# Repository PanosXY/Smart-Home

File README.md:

# Smart-Home
Smart Home combines a lot of technologies such as Internet, Electronics, Wireless communication, Serial communication, Databases, Raspberry Pi &amp; Linux and several programming languages (Python, PHP, Embedded C)

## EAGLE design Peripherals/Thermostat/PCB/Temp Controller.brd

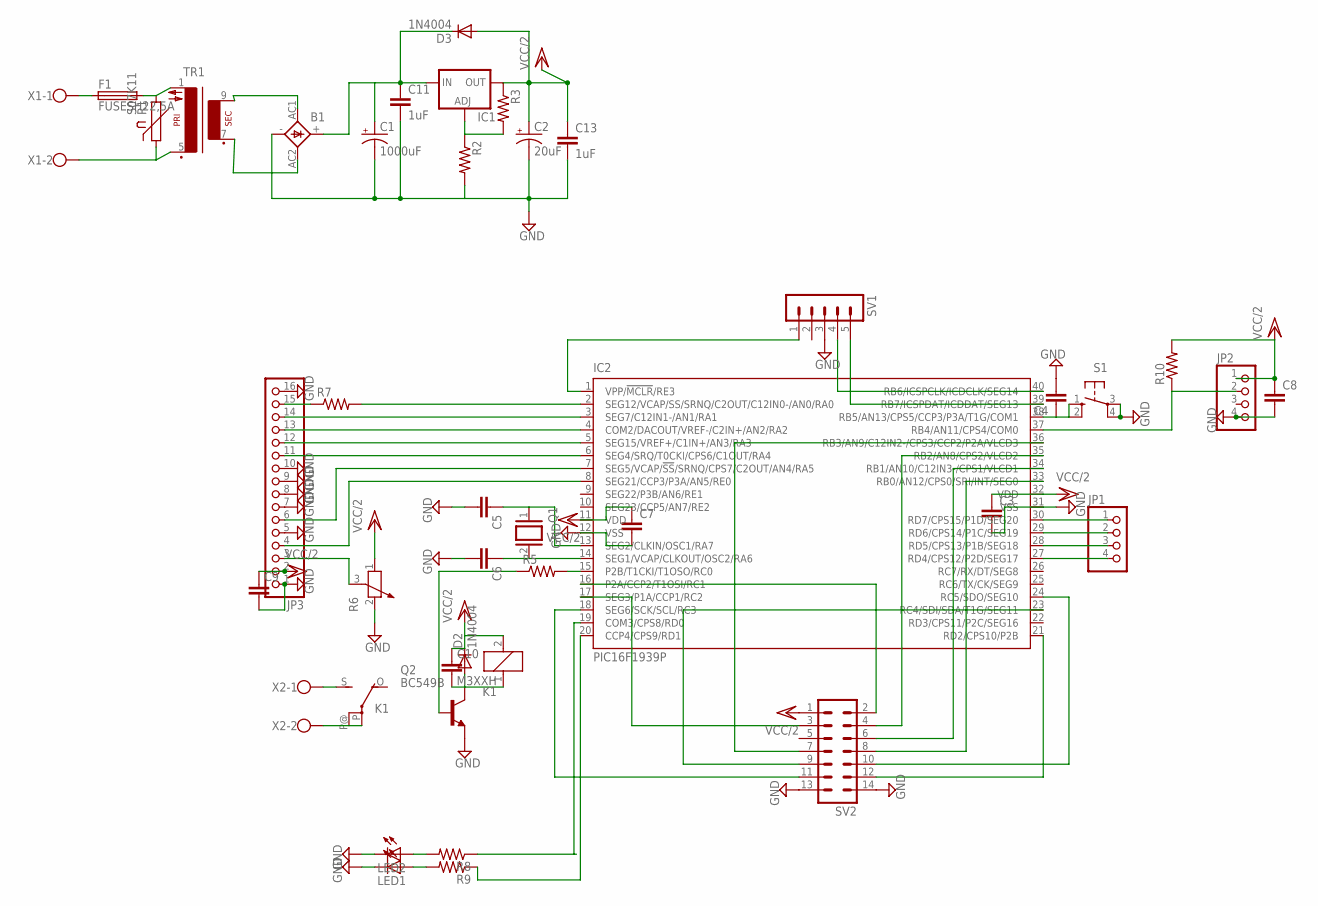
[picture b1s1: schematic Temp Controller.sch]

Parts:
B1: 1KAB
C1: 1000uF; E5-13
C2: 20uF; E5-6
C3, C4, C7, C8, C9, C10: C-EU025-030X050; C025-030X050
C5, C6: C2.5/2; C2.5-2
C11, C13: 1uF; C025-030X050
D2, D3: 1N4004; DO41-10
F1: FUSESH22,5A; SH22,5A
IC1: LM317TS; 317TS
IC2: PIC16F1939P; DIL40
JP1, JP2: PINHD-1X4; 1X04
JP3: PINHD-1X16; 1X16
K1: M3XXH
LED1, LED2: LED3MM
Q1: XTAL/S; QS
Q2: BC549B; TO92-EBC
R1: S07K11
R2, R3, R5, R7, R8, R9, R10: R-US_0207/10; 0207/10
R6: POTENTIOMETER_PT-10; PT-10
S1: 10-XX; B3F-10XX
SV1: MA05-1
SV2: MA07-2
TR1: VV11
X1, X2: W237-02P; W237-132

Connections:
GND: B1.-, C1.-, C2.-, C3.2, C4.2, C5.2, C6.2, C7.2, C8.2, C9.2, C11.2, C13.2, IC2.12 (VSS), IC2.31 (VSS), JP2.4, JP3.1, JP3.5, JP3.7, JP3.8, JP3.9, JP3.10, JP3.16, LED1.K (C), LED2.K (C), Q2.E, R2.2, R6.2, S1.3, S1.4 (P1), SV1.3, SV2.13, SV2.14
unnamed: F1.1, X1.1
unnamed: F1.2, R1.2, TR1.1
unnamed: R1.1, TR1.5 (P2), X1.2
unnamed: IC2.33 (RB0/AN12/CPS0/SRI/INT/SEG0), SV2.8
unnamed: B1.AC1, TR1.9 (S4)
unnamed: B1.AC2, TR1.7 (S3)
unnamed: IC2.30 (RD7/CPS15/P1D/SEG20), JP1.1
unnamed: B1.+, C1.+, C11.1, D3.C, IC1.3 (IN)
unnamed: IC2.34 (RB1/AN10/C12IN3-/CPS1/VLCD1), SV2.6
unnamed: IC2.18 (SEG6/SCK/SCL/RC3), SV2.11
unnamed: IC2.1 (VPP/!MCLR!/RE3), SV1.1
unnamed: IC2.40 (RB6/ICSPCLK/ICDCLK/SEG14), SV1.4
unnamed: IC2.39 (RB7/ICSPDAT/ICDDAT/SEG13), SV1.5
unnamed: C5.1, IC2.13 (SEG2/CLKIN/OSC1/RA7), Q1.1
unnamed: C6.1, IC2.14 (SEG1/VCAP/CLKOUT/OSC2/RA6), Q1.2
unnamed: IC2.2 (SEG12/VCAP/SS/SRNQ/C2OUT/C12IN0-/AN0/RA0), R7.2
unnamed: IC2.29 (RD6/CPS14/P1C/SEG19), JP1.2
unnamed: IC2.23 (RC4/SDI/SDA/T1G/SEG11), SV2.9
unnamed: IC2.24 (RC5/SDO/SEG10), SV2.10
unnamed: IC2.21 (RD2/CPS10/P2B), SV2.12
unnamed: IC2.16 (P2A/CCP2/T1OSI/RC1), SV2.2
unnamed: IC2.17 (SEG3/P1A/CCP1/RC2), SV2.3
unnamed: JP3.15, R7.1
unnamed: IC2.36 (RB3/AN9/C12IN2-/CPS3/CCP2/P2A/VLCD3), SV2.7
unnamed: IC2.35 (RB2/AN8/CPS2/VLCD2), SV2.4
unnamed: IC2.3 (SEG7/C12IN1-/AN1/RA1), JP3.14
unnamed: IC2.4 (COM2/DACOUT/VREF-/C2IN+/AN2/RA2), JP3.13
unnamed: IC2.5 (SEG15/VREF+/C1IN+/AN3/RA3), JP3.12
unnamed: IC2.6 (SEG4/SRQ/T0CKI/CPS6/C1OUT/RA4), JP3.11
unnamed: IC2.7 (SEG5/VCAP/!SS!/SRNQ/CPS7/C2OUT/AN4/RA5), JP3.6
unnamed: IC2.8 (SEG21/CCP3/P3A/AN5/RE0), JP3.4
unnamed: JP3.3, R6.3
unnamed: IC2.28 (RD5/CPS13/P1B/SEG18), JP1.3
unnamed: IC1.1 (ADJ), R2.1, R3.2
unnamed: LED1.A, R9.2
unnamed: LED2.A, R8.2
unnamed: IC2.27 (RD4/CPS12/P2D/SEG17), JP1.4
unnamed: IC2.20 (CCP4/CPS9/RD1), R9.1
unnamed: IC2.19 (COM3/CPS8/RD0), R8.1
unnamed: C4.1, IC2.38 (RB5/AN13/CPS5/CCP3/P3A/T1G/COM1), S1.1 (S), S1.2 (S1)
unnamed: C10.2, D2.A, K1.1, Q2.C
unnamed: IC2.15 (P2B/T1CKI/T1OSO/RC0), R5.2
unnamed: Q2.B, R5.1
unnamed: K1.S, X2.1
unnamed: K1.P, K1.P@, X2.2
unnamed: IC2.37 (RB4/AN11/CPS4/COM0), JP2.2, R10.1
VCC/2: C2.+, C3.1, C7.1, C8.1, C9.1, C10.1, C13.1, D2.C, D3.A, IC1.2 (OUT), IC2.11 (VDD), IC2.32 (VDD), JP2.1, JP3.2, K1.2, R3.1, R6.1, R10.2, SV2.1

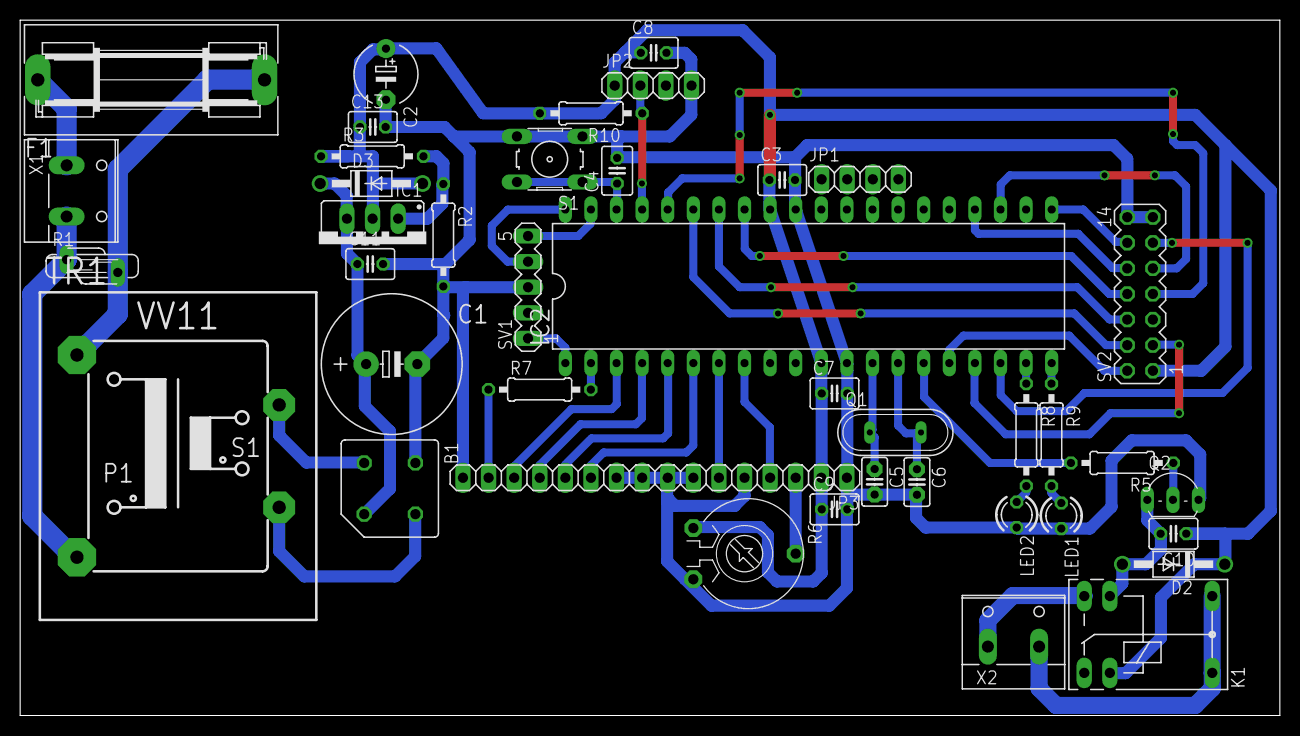
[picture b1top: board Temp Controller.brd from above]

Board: 2 copper layers, 125.0 x 69.0 mm, 41 parts (0 on the bottom side), 48 nets.

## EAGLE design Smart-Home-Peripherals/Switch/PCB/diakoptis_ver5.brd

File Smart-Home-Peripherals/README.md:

Smart-Home-Peripherals
======================

Firmware and PCBs of Peripherals of Smart Home

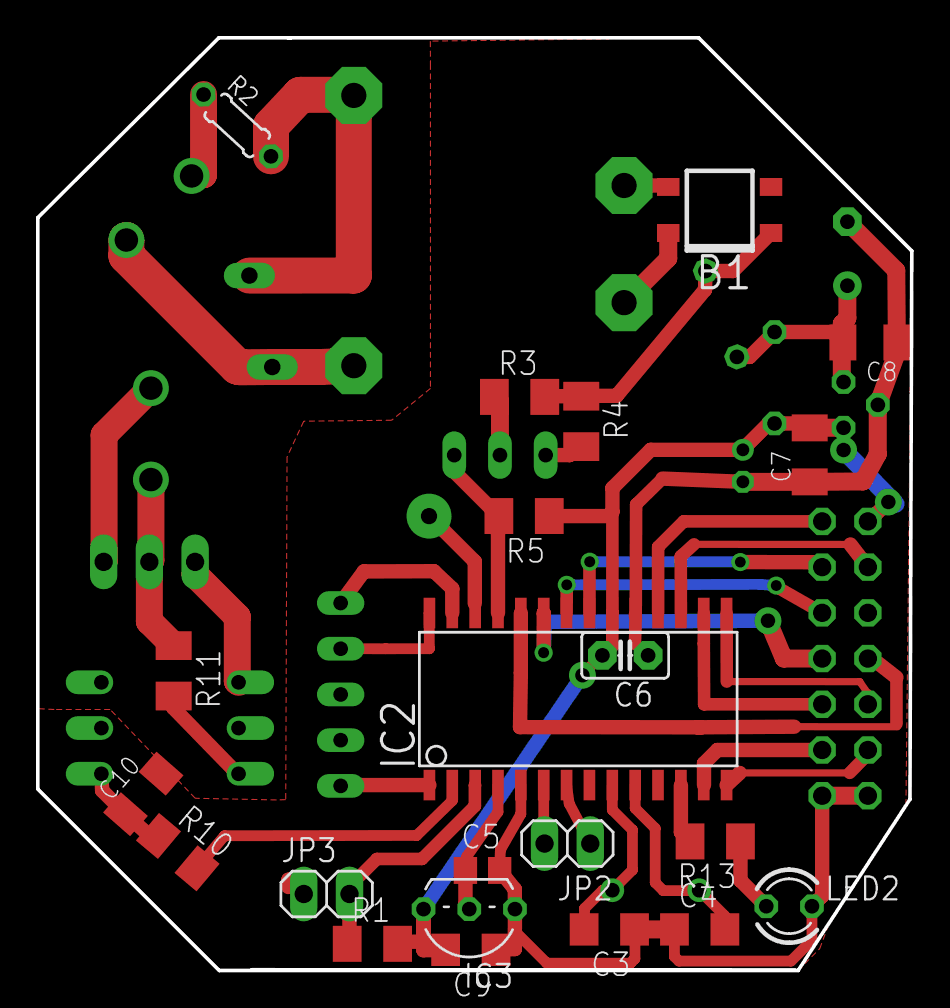
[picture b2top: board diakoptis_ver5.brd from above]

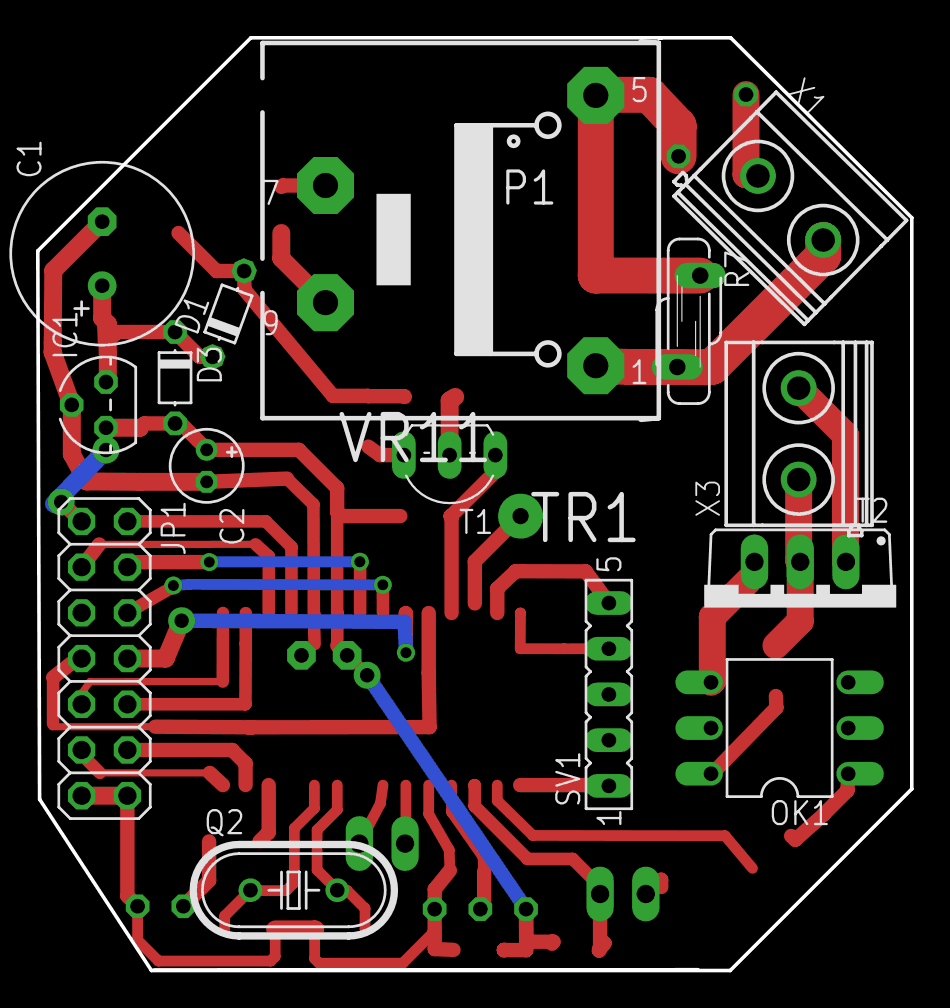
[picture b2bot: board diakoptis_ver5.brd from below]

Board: 2 copper layers, 48.6 x 51.8 mm, 37 parts (15 on the bottom side), 38 nets.

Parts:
B1: RECTIFIER-S250; TO-269AA
C1: 680uF; E3,5-10
C2: 20uF; E1,8-4
C3, C4: 22pF; C1206
C5: 100nF; C0805
C6: 100nF; C2.5-2
C7, C8, C10: 100nF; C1206K
C9: 100nF; C1206
D1, D3: 1N4002; D-5
IC1: 78L05Z; TO92
IC2: PIC16F1938SO; SO28W
IC3: DS18B20; TO92-
JP1: 2X07
JP2, JP3: 1X02
LED2: RED; LED3MM
OK1: MOC3012M; DIL06
Q2: HC49U70
R1: 15; M1206
R2: 0204/5
R3: 10k; M1206
R4, R5: 1k; M1206
R7: S07K11
R10: 130; M1206
R11: 260; M1206
R13: 120; M1206
SV1: FE05-1
T1: TO92-CBE
T2: BT138-V; TO220BV
TR1: VR11MINI
X1, X3: MKDSN1,5/2-5,08

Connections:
GND: B1.-, C1.-, C2.-, C3.1, C4.1, C5.2, C6.1, C7.1, C8.1, C9.1, C10.2, IC1.2, IC2.5, IC2.8, IC2.11, IC2.19, IC3.1, JP1.13, JP1.14, JP3.1, LED2.K, OK1.2, R4.2, SV1.3, T1.E
unnamed: IC2.3, JP3.2, R1.1
unnamed: B1.AC2, TR1.7
unnamed: B1.AC1, TR1.9
unnamed: B1.+, D1.A, R3.2, R4.1
unnamed: C1.+, C8.2, D1.C, D3.C, IC1.3
unnamed: R7.2, TR1.1, X1.2
unnamed: IC2.13, JP1.12
unnamed: R3.1, T1.B
unnamed: IC2.18, JP1.2
unnamed: C3.2, IC2.9, Q2.2
unnamed: C4.2, IC2.10, Q2.1
unnamed: IC2.14, JP1.11
unnamed: IC2.15, JP1.9
unnamed: IC2.21, JP1.4
unnamed: IC2.22, JP1.6
unnamed: IC2.23, JP1.8
unnamed: IC2.24, JP1.7
unnamed: IC2.16, JP1.10
unnamed: IC2.17, JP1.3
unnamed: R2.2, R7.1, TR1.5
unnamed: IC2.1, SV1.1
unnamed: IC2.2, R10.2
unnamed: IC2.25, R5.2, T1.C
unnamed: R2.1, X1.1
unnamed: C5.1, IC2.4, IC3.2
unnamed: IC2.12, R13.2
unnamed: IC2.27, SV1.5
unnamed: IC2.28, SV1.4
unnamed: IC2.6, JP2.2
unnamed: IC2.7, JP2.1
unnamed: C10.1, OK1.1, R10.1
unnamed: OK1.4, T2.G
unnamed: OK1.6, R11.2
unnamed: R11.1, T2.T2, X3.1
unnamed: T2.T1, X3.2
unnamed: LED2.A, R13.1
VCC: C2.+, C6.2, C7.2, C9.2, D3.A, IC1.1, IC2.20, IC3.3, JP1.1, R1.2, R5.1

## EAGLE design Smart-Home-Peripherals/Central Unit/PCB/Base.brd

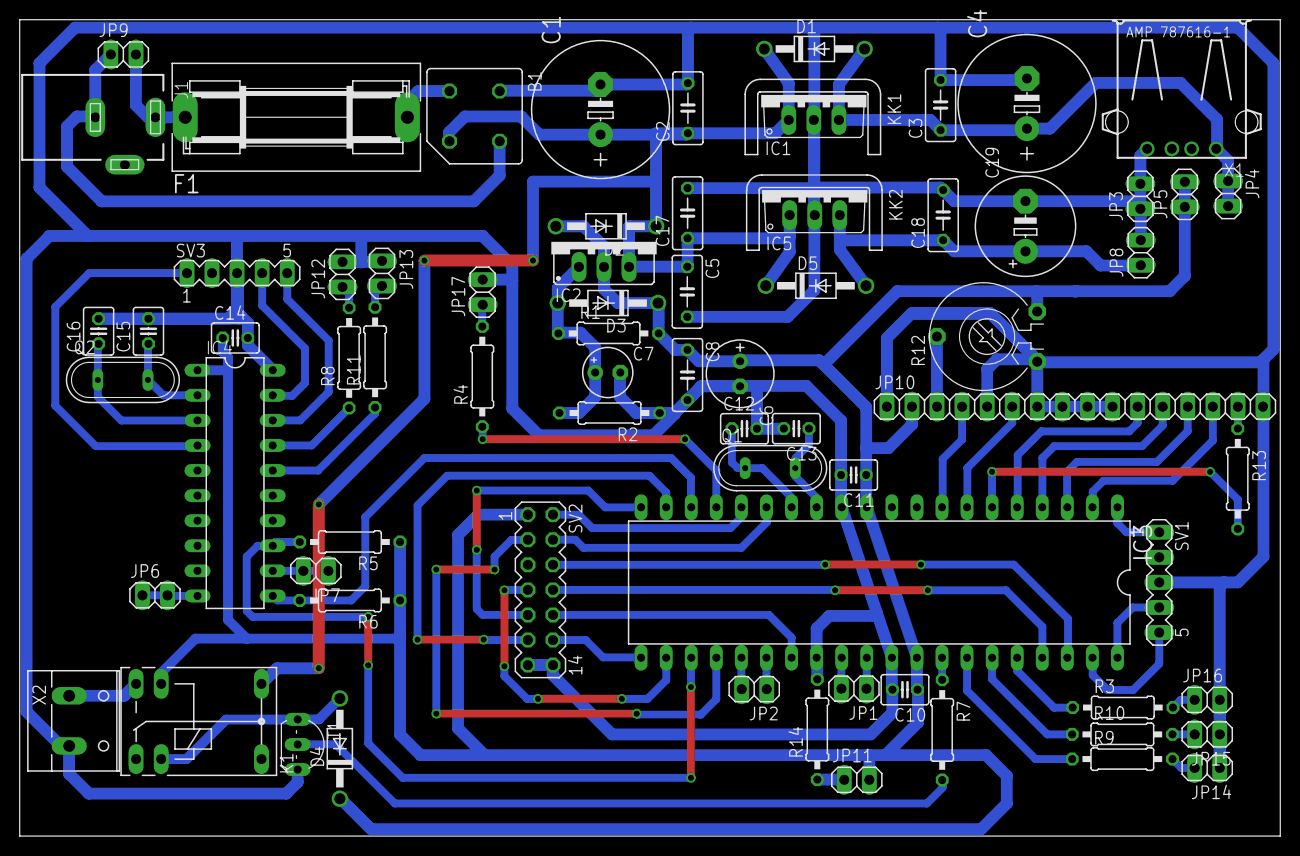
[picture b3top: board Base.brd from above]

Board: 2 copper layers, 127.7 x 82.7 mm, 73 parts (0 on the bottom side), 63 nets.

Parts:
B1: 1KAB
C1, C4: E5-13
C2, C3, C5, C8, C17, C18: C050-030X075
C6: E2,5-7
C7: E2,5-5
C10, C11, C12, C13, C14, C15, C16: C025-030X050
C19: E5-10,5
D1, D2, D3, D4, D5: 1N4004; DO41-10
F1: FUSESH22,5A; SH22,5A
IC1, IC5: 7805TV; TO220V
IC2: 317TS
IC3: PIC18LF45K22; DIL40
IC4: PIC18LF14K22; DIL20
J1: DCJ0202
JP1, JP2, JP3, JP4, JP5, JP6, JP7, JP8, JP9, JP11, JP12, JP13, JP14, JP15, JP16, JP17: 1X02
JP10: 1X16
K1: M3XXH
KK1, KK2: D03S
Q1, Q2: QS
R1, R2, R3, R4, R5, R6, R7, R8, R9, R10, R11, R13, R14: 0207/10
R12: PT-10
SV1, SV3: MA05-1
SV2: MA07-2
T1: TO92-CBE
X1: USB
X2: W237-132

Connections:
GND: B1.-, C1.-, C2.2, C3.2, C4.-, C5.2, C6.-, C7.-, C8.2, C10.2, C11.2, C12.2, C13.2, C14.2, C15.2, C16.2, C17.2, C18.2, C19.-, IC1.2, IC3.12, IC3.28, IC3.31, IC4.20, IC5.2, JP3.1, JP3.2, JP8.2, JP10.1, JP10.5, JP10.7, JP10.8, JP10.9, JP10.10, JP10.16, JP12.2, JP13.1, JP14.1, JP15.1, JP16.2, JP17.2, R2.1, R12.1, R14.2, SV1.3, SV2.13, SV2.14, SV3.3, T1.E, X1.4, X2.2
unnamed: F1.1, J1.1, JP9.2
unnamed: B1.AC1, F1.2
unnamed: B1.AC2, J1.3, JP9.1
unnamed: IC3.1, SV1.1
unnamed: C7.+, D3.A, IC2.1, R1.1, R2.2
unnamed: IC3.40, SV1.4
unnamed: IC3.39, SV1.5
unnamed: C13.1, IC3.13, Q1.2
unnamed: C12.1, IC3.14, Q1.1
unnamed: JP16.1, R3.2
unnamed: IC3.26, JP2.1
unnamed: IC3.25, JP2.2
unnamed: IC3.30, JP1.1
unnamed: IC3.29, JP1.2
unnamed: JP15.2, R10.2
unnamed: JP14.2, R9.2
unnamed: JP12.1, R8.2
unnamed: IC3.19, SV2.11
unnamed: IC3.20, SV2.9
unnamed: IC3.27, SV2.10
unnamed: IC4.19, SV3.4
unnamed: IC4.18, SV3.5
unnamed: C15.1, IC4.2, Q2.2
unnamed: C16.1, IC4.3, Q2.1
unnamed: IC4.4, SV3.1
unnamed: IC3.23, IC4.13, R5.2
unnamed: IC3.18, IC4.11, R6.2
unnamed: IC3.16, SV2.2
unnamed: R7.2, T1.B
unnamed: D4.A, K1.2, T1.C
unnamed: K1.S, X2.1
unnamed: IC3.21, SV2.12
unnamed: IC3.37, SV2.8
unnamed: IC3.38, SV2.6
unnamed: JP13.2, R11.2
unnamed: IC4.10, JP6.1, JP6.2
unnamed: C18.1, C19.+, D5.A, IC5.3, JP8.1
unnamed: IC3.15, SV2.4
unnamed: IC3.24, SV2.3
unnamed: IC3.22, SV2.7
unnamed: IC3.33, R7.1
unnamed: IC3.34, R9.1
unnamed: IC4.12, JP7.1, JP7.2
unnamed: IC3.35, R10.1
unnamed: IC3.36, R3.1
unnamed: JP17.1, R4.2
unnamed: IC4.17, R8.1
unnamed: IC4.16, R11.1
unnamed: IC3.2, JP10.14
unnamed: JP10.3, R12.3
unnamed: IC3.7, JP10.6
unnamed: IC3.8, JP10.4
unnamed: IC3.3, JP10.13
unnamed: IC3.4, JP10.12
unnamed: IC3.5, JP10.11
unnamed: IC3.6, R13.2
unnamed: JP10.15, R13.1
unnamed: JP11.1, R14.1
unnamed: IC3.17, R4.1
VCC: C3.1, C4.+, D1.A, IC1.3, JP4.1, JP4.2, X1.1
VDD: B1.+, C1.+, C2.1, C5.1, C17.1, D1.C, D2.C, D5.C, IC1.1, IC2.3, IC5.1, K1.P@
VEE: C6.+, C8.1, C10.1, C11.1, C14.1, D2.A, D3.C, D4.C, IC2.2, IC3.11, IC3.32, IC4.1, JP5.1, JP5.2, JP10.2, JP11.2, K1.1, R1.2, R5.1, R6.1, R12.2, SV2.1

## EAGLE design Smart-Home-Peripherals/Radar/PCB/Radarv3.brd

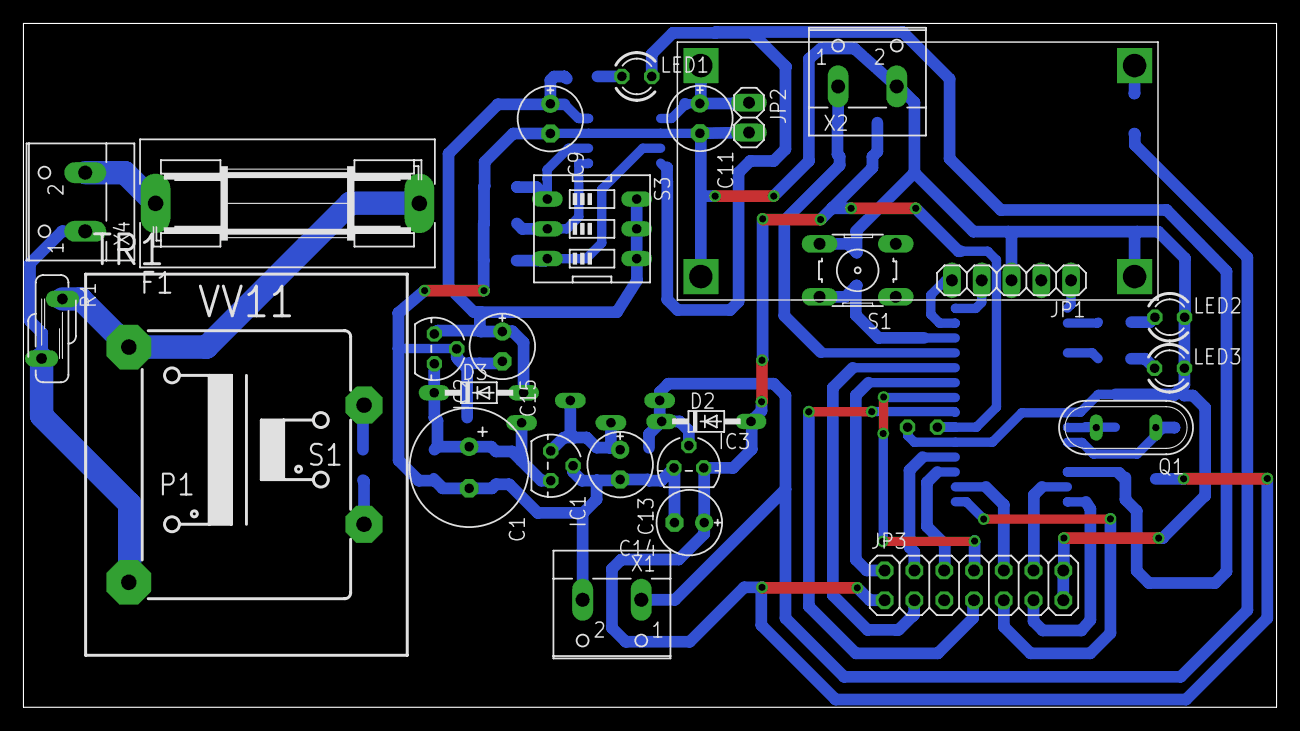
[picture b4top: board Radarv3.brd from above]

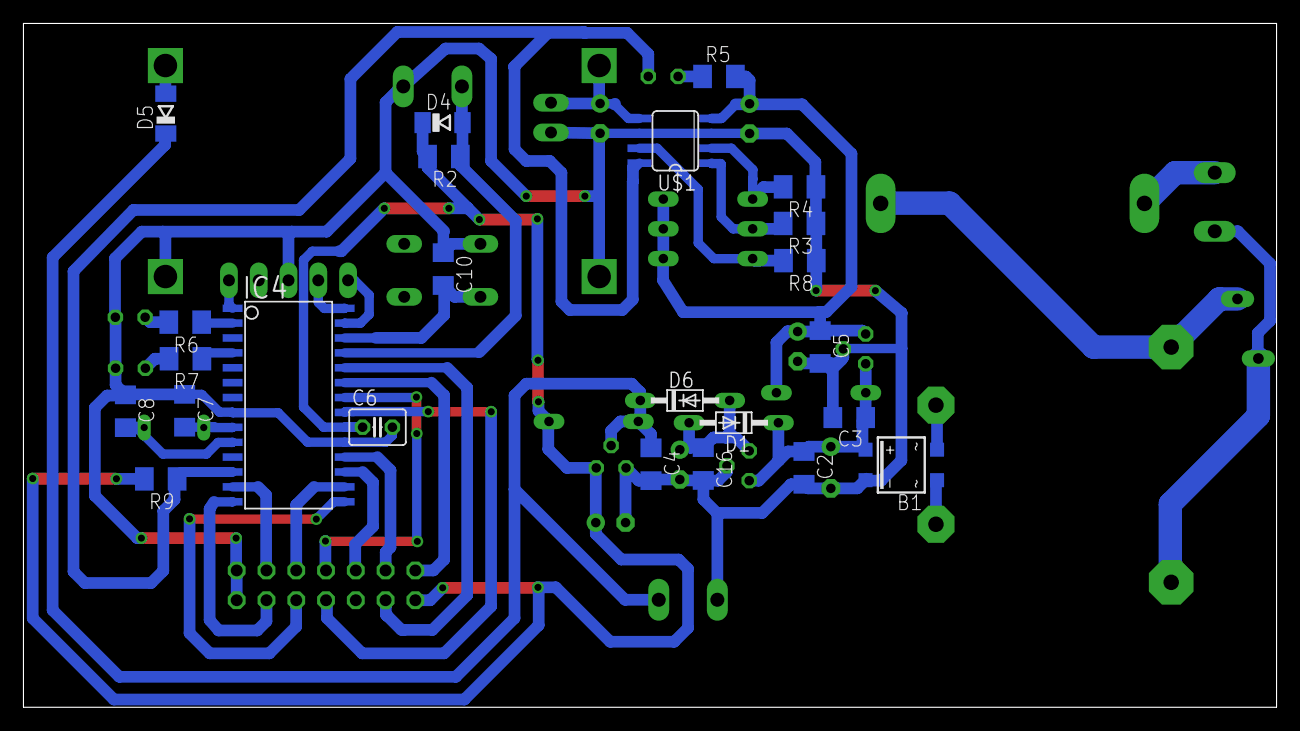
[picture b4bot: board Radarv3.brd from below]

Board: 2 copper layers, 106.9 x 58.3 mm, 51 parts (24 on the bottom side), 39 nets.

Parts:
B1: MB4S; SOIC-4
C1: E3,5-10
C2, C3, C4, C5, C7, C8, C10, C16: C1206
C6: C025-030X050
C9, C11, C13, C14, C15: E2,5-6E
D1, D2, D3, D6: BAT81; DO34-7
D4, D5: PMLL4150; SOD80C
F1: FUSESH22,5A; SH22,5A
IC1: 7812L; TO92
IC2: 7805L; TO92
IC3: MCP1702; TO-92
IC4: PIC16F1938SO; SO28W
JP1: 1X05
JP2: BATTERY; 1X02
JP3: 2X07
LED1, LED2, LED3: LED3MM
Q1: QS
R1: S07K40
R2, R3, R4, R5, R6, R7, R8, R9: M1206
S1: B3F-10XX
S3: EDG-03
TR1: VV11
U$1: MAX1811; SO08
U$2: STEP_UP_MODULE; STEP_UP_MOD
X1, X2, X4: W237-102

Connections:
CHG_LOGIC_OUT: IC4.12, LED1.K, R9.1, U$1.8
GND: B1.-, C1.-, C2.2, C3.2, C4.2, C5.2, C6.2, C7.1, C8.1, C9.-, C10.1, C11.-, C13.-, C14.-, C15.-, C16.2, IC1.2, IC2.2, IC3.1, IC4.8, IC4.19, JP1.3, JP2.2, JP3.13, JP3.14, LED2.K, LED3.K, R3.1, R4.1, R8.1, S1.4, U$1.3, U$1.6, U$2.P$2, U$2.P$3, X1.2, X2.2
unnamed: F1.1, X4.2
unnamed: F1.2, R1.1, TR1.1
unnamed: R1.2, TR1.5, X4.1
unnamed: B1.~2, TR1.9
unnamed: B1.~1, TR1.7
unnamed: C7.2, IC4.9, Q1.2
unnamed: C8.2, IC4.10, Q1.1
unnamed: B1.+, C1.+, C2.1, C3.1, D1.C, D3.C, IC1.3, IC2.3
unnamed: D4.A, IC4.25, R2.1, X2.1
unnamed: LED1.A, R5.1
unnamed: C10.2, IC4.26, S1.2
unnamed: IC4.1, JP1.1
unnamed: IC4.27, JP1.5
unnamed: IC4.28, JP1.4
unnamed: R8.2, S3.3, U$1.7
unnamed: R3.2, S3.2, U$1.1
unnamed: R4.2, S3.1, U$1.2
unnamed: C13.+, C16.1, D1.A, D6.A, IC1.1
unnamed: IC4.2, R6.1
unnamed: IC4.4, R7.1
unnamed: LED2.A, R6.2
unnamed: LED3.A, R7.2
unnamed: IC4.14, JP3.11
unnamed: C11.+, JP2.1, U$1.5, U$2.P$1
unnamed: IC4.16, JP3.10
unnamed: IC4.15, JP3.9
unnamed: IC4.21, JP3.7
unnamed: IC4.22, JP3.8
unnamed: IC4.13, JP3.12
unnamed: IC4.17, JP3.6
unnamed: IC4.18, JP3.4
unnamed: IC4.23, JP3.2
unnamed: IC4.24, JP3.3
unnamed: D5.A, U$2.P$4
VCC: C4.1, D2.C, D5.C, D6.C, IC3.2, X1.1
VDD: C5.1, C9.+, C15.+, D3.A, IC2.1, R5.2, S3.4, S3.5, S3.6, U$1.4
VEE: C6.1, C14.+, D2.A, D4.C, IC3.3, IC4.20, JP3.1, R2.2, R9.2

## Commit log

2015-12-12 Updated .gitignore
